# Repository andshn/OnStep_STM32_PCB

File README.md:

# OnStep STM32 PCB 

This is a PCB for [OnStep](https://github.com/hjd1964/OnStep),
designed for [1455N1201](https://www.hammfg.com/part/1455N1201) case.
In the board use XLR connectors for steper drivers.
The DB9 connector use for the hand controller.

The directory structure is as follows:
         
      onstep_pcb/       - KiCad project files for the board
      end_plates/       - Case end plates drawings as KiCad PCB files
      project_outputs/  - Gerbers, BOM, PDFs, etc

Note: this project contains partially modified elements
from the [KiCad Libraries](https://gitlab.com/kicad/libraries).

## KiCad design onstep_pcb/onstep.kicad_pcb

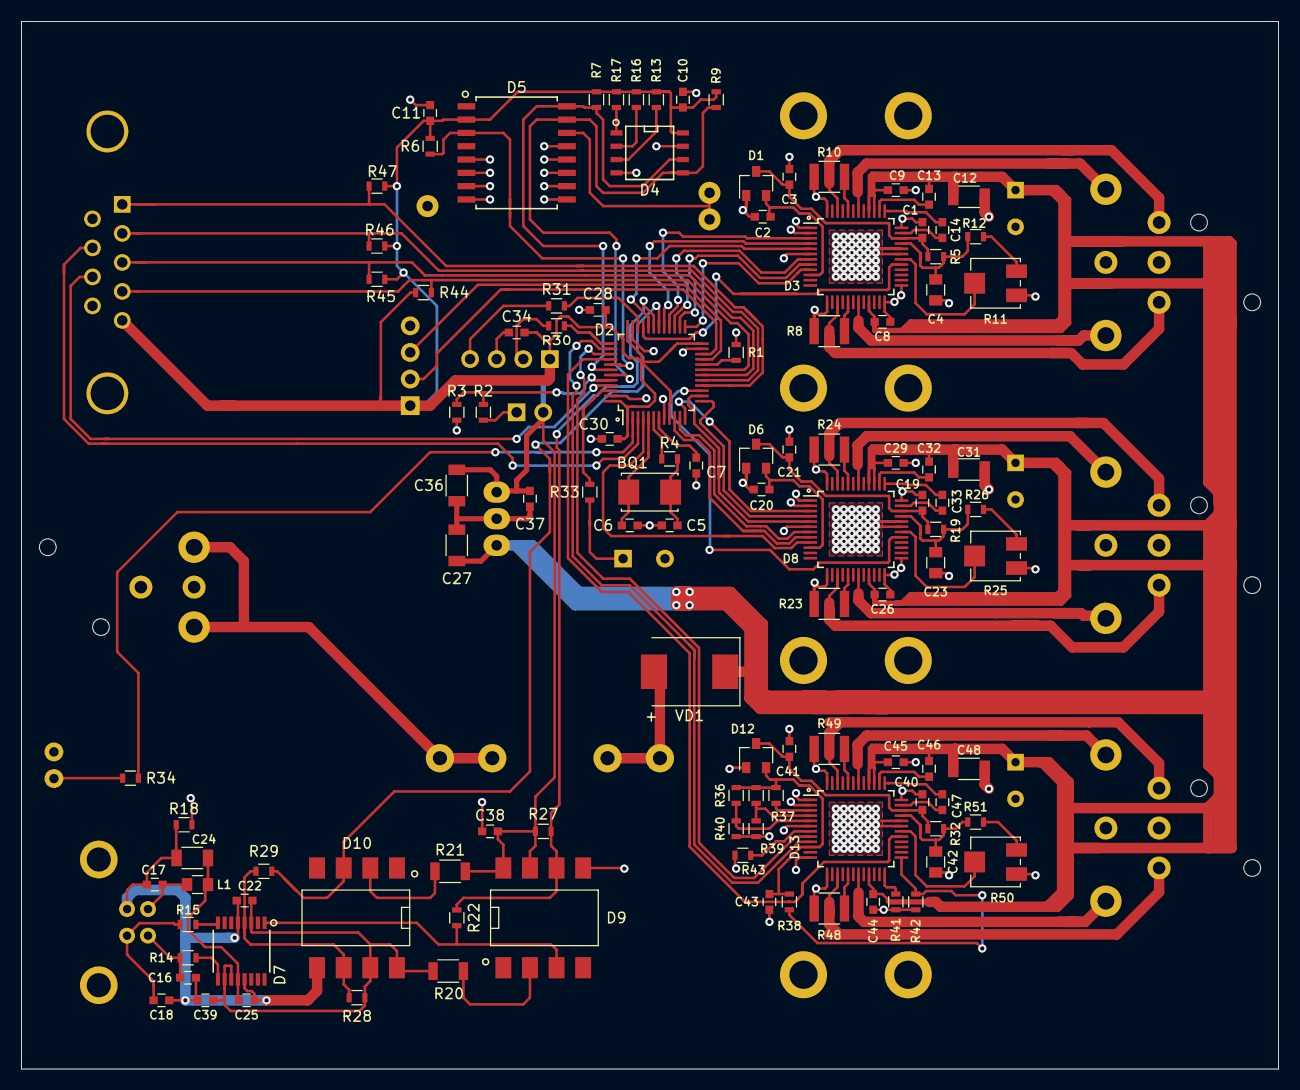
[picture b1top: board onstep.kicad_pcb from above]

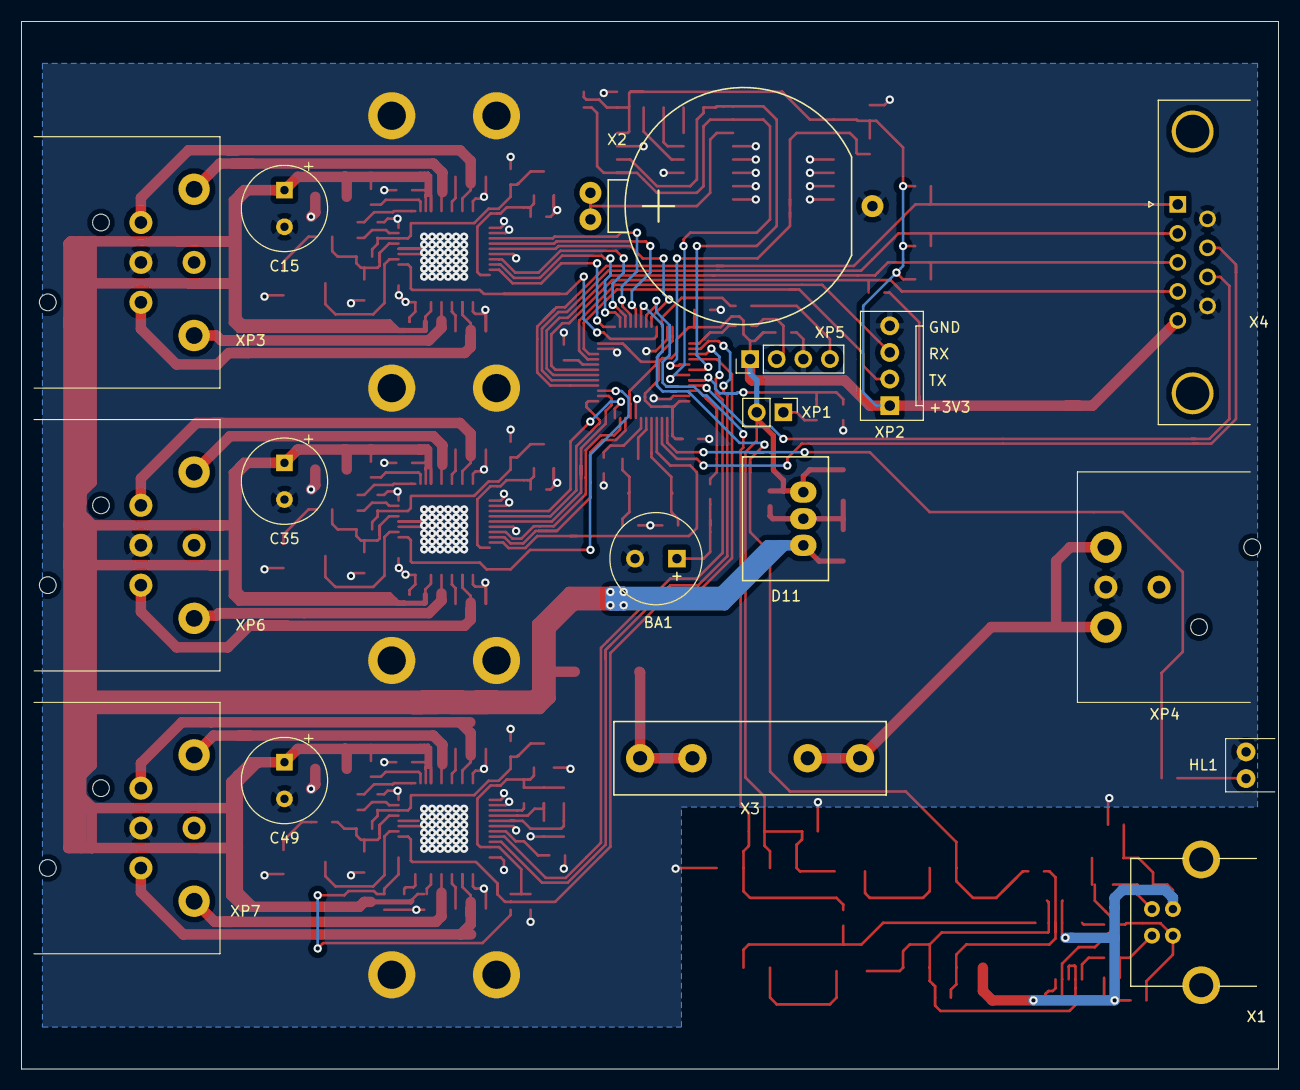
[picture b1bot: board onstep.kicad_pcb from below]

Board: 2 copper layers, 120.0 x 100.0 mm, 129 parts (17 on the bottom side), 114 nets.

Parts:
BA1: Speaker; Buzzer_CST-951AP
BQ1: 8 MHz; Crystal_SMD_5032-2pin_5.0x3.2mm
C1, C2, C3, C19, C20, C21, C40, C41, C43: 1 uF; C_0603
C4, C23, C42: 4.7 uF; C_0805
C5, C6: 24 pF; C_0603
C7, C8, C9, C10, C11, C13, C22, C25, C26, C28, C29, C30, C32, C34, C37, C38, C39, C44, C45, C46: 0.1 uF; C_0603
C12, C24, C31, C48: 4.7 uF; C_1206
C14, C33, C47: 0.022 uF; C_0603
C15, C35, C49: 100 uF; CP_Radial_D8.0mm_P3.50mm
C16, C18: 47 pF; C_0603
C17: 0.01 uF; C_0603
C27, C36: 10 uF; C_1206
D1, D6: MCP1700; SOT-23
D2: STM32F103C8T6; TQFP-48_7x7mm_Pitch0.5mm
D3, D8, D13: TMC2130; TQFP-48_7x7mm_Pitch0.5mm
D4: M24C32; SOIC-8-N
D5: DS3231; SOIC-16W_7.5x10.3mm_Pitch1.27mm
D7: FT230; SSOP-16_3.9x4.9mm_Pitch0.635mm
D9, D10: 6N137; SMD-8
D11: P78E03; CUI_P78E
D12: MCP1700T; SOT-23
HL1: LED; LED_WP934CB
L1: BLM21AG601SN1D; L_0805
R1, R2, R27, R28, R34: 1k; R_0603
R3, R6, R7, R9, R13, R16, R17: 10k; R_0603
R4: 390; R_0603
R5, R19, R32: 2.2; R_0603
R8, R10, R23, R24, R48, R49: 0.12; R_1210
R11, R25, R50: 20k; Potentiometer_Bourns_3314J_Vertical
R12, R26, R51: 20k; R_0603
R14, R15: 27; R_0603
R18, R22, R29, R35, R36, R39, R40, R42: DNI; R_0603
R20, R21: 220; R_1206
R30, R31: 100; R_0603
R33: 470; R_0603
R37, R38, R41, R43: 0; R_0603
R44, R45, R46, R47: 2.2k; R_0603
VD1: STPS5L60S; D_SMC
X1: "USB"; USB_B
X2: Battery Holder; CR2032_120591-1
X3: "FUSE"; Fuseholder5x20
X4: Conn_01x09; DSUB-9_Female_Horizontal_P2.77x2.84mm_EdgePinOffset9.90mm_H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
XP1: "Bootloader"; Pin_Header_Straight_1x02_Pitch2.54mm
XP2: "UART"; Pin_Header_640456-4
XP3: "DRV1"; NC5MBH
XP4: "12V"; NC3MAAH
XP5: "SWD"; Pin_Header_Straight_1x04_Pitch2.54mm
XP6: "DRV2"; NC5MBH
XP7: "DRV3"; NC5MBH

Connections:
+3,3V_USB: C22.2, C39.2, D7.3, D7.10, D7.11, D10.7, D10.8, R20.2, R28.2
+3V3: C10.2, C11.2, C28.2, C30.2, C34.2, C36.2, C37.2, C38.2, D2.1, D2.9, D2.24, D2.36, D2.48, D4.8, D5.2, D9.7, D9.8, D11.3, R6.2, R7.2, R9.2, R13.1, R16.1, R17.1, R21.2, R27.2, R44.1, R45.1, R46.1, R47.1, X4.5, XP1.2, XP2.1, XP5.1
+VM: C8.2, C9.2, C12.2, C13.2, C15.1, C26.2, C27.2, C29.2, C31.2, C32.2, C35.1, C44.2, C45.2, C46.2, C48.2, C49.1, D3.21, D3.39, D3.40, D8.21, D8.39, D8.40, D11.1, D13.21, D13.39, D13.40, VD1.1
/BOOT0: D2.44, R2.2, R3.2
/BOOT1: D2.20, R1.2
/DRV1_DIR: D2.25, D3.9
/DRV1_ENN: D2.33, D3.29
/DRV1_MISO: D2.27, D3.7
/DRV1_MOSI: D2.32, D3.5
/DRV1_NPCS: D2.28, D3.3
/DRV1_SPCK: D2.29, D3.4
/DRV1_STEP: D2.26, D3.8
/DRV2_DIR: D2.4, D8.9
/DRV2_ENN: D2.15, D8.29
/DRV2_MISO: D2.11, D8.7
/DRV2_MOSI: D2.14, D8.5
/DRV2_NPCS: D2.12, D8.3
/DRV2_SPCK: D2.13, D8.4
/DRV2_STEP: D2.10, D8.8
/DRV3_CFG0: D13.7, R43.2
/DRV3_CFG1: D13.5, R36.2, R40.2
/DRV3_CFG2: D13.4, R35.2, R39.2
/DRV3_CFG3: D13.3, R37.2
/DRV3_CFG4: D13.24, R41.2
/DRV3_CFG5: D13.25, R38.2, R42.2
/DRV3_DIR: D2.38, D13.9
/DRV3_ENN: D2.40, D13.29
/DRV3_STEP: D2.39, D13.8
/DRV3_VIO: C43.1, D12.2, D13.10, R35.1, R36.1, R37.1, R38.1
/HLED: D2.2, R34.2
/OSC_IN: BQ1.2, C6.2, D2.5
/OSC_OUT: D2.6, R4.2
/PECIDX: D2.3, X4.7
/RETICLE: D2.45, X4.8
/SCL: D2.42, D4.6, D5.16, R7.1
/SDA: D2.43, D4.5, D5.15, R9.1
/SQW: D2.41, D5.3, R6.1
/ST4_RA+: D2.19, R44.2, X4.4
/ST4_RA-: D2.16, R47.2, X4.1
/ST-4_DEC+: D2.18, R45.2, X4.3
/ST-4_DEC-: D2.17, R46.2, X4.2
/SWCLK: D2.37, R30.2
/SWDIO: D2.34, R31.2
/TONE: D2.46, R33.2
/UART0_RX: D2.30, D10.3, R29.1
/UART0_TX: D2.31, D9.6, R22.1, R27.1
/UART1_RX: D2.21, XP2.3
/UART1_TX: D2.22, XP2.2
GND: BA1.2, C1.1, C2.1, C3.1, C4.1, C5.1, C6.1, C7.1, C8.1, C9.1, C10.1, C11.1, C12.1, C15.2, C19.1, C20.1, C21.1, C23.1, C26.1, C27.1, C28.1, C29.1, C30.1, C31.1, C34.1, C35.2, C36.1, C37.1, C38.1, C40.1, C41.1, C42.1, C43.2, C44.1, C45.1, C48.1, C49.2, D1.1, D2.8, D2.23, D2.35, D2.47, D3.1, D3.2, D3.6, D3.13, D3.24, D3.25, D3.31, D3.32, D3.36, D3.48, D4.4, D4.7, D5.5, D5.6, D5.7, D5.8, D5.9, D5.10, D5.11, D5.12, D5.13, D6.1, D8.1, D8.2, D8.6, D8.13, D8.24, D8.25, D8.31, D8.32, D8.36, D8.48, D9.5, D11.2, D12.1, D13.1, D13.2, D13.6, D13.12, D13.13, D13.31, D13.32, D13.36, D13.48, HL1.1, R1.1, R3.1, R8.1, R10.1, R11.1, R18.1, R23.1, R24.1, R25.1, R39.1, R40.1, R41.1, R42.1, R43.1, R48.1, R49.1, R50.1, X2.2, X4.6, X4.9, XP2.4, XP3.6, XP4.3, XP5.3, XP6.6, XP7.6
GNDA: C16.1, C17.1, C18.1, C22.1, C24.1, C25.1, C39.1, D7.5, D7.13, D10.5, R18.2, X1.4
unnamed: BA1.1, R33.1
unnamed: BQ1.1, C5.2, R4.1
unnamed: C1.2, C3.2, D1.3, D3.34, R5.1
unnamed: C2.2, D1.2, D3.10
unnamed: C4.2, D3.33, R5.2, R12.1
unnamed: C7.2, D2.7
unnamed: C13.1, D3.38
unnamed: C14.1, D3.35
unnamed: C14.2, D3.37
unnamed: C16.2, R14.2, X1.2
unnamed: C17.2, L1.1, X1.1
unnamed: C18.2, R15.2, X1.3
unnamed: C19.2, C21.2, D6.3, D8.34, R19.1
unnamed: C20.2, D6.2, D8.10
unnamed: C23.2, D8.33, R19.2, R26.1
unnamed: C24.2, C25.2, D7.12, L1.2
unnamed: C32.1, D8.38
unnamed: C33.1, D8.35
unnamed: C33.2, D8.37
unnamed: C40.2, C41.2, D12.3, D13.34, R32.1
unnamed: C42.2, D13.33, R32.2, R51.1
unnamed: C46.1, D13.38
unnamed: C47.1, D13.35
unnamed: C47.2, D13.37
unnamed: D3.15, XP3.4
unnamed: D3.17, R8.2
unnamed: D3.19, XP3.5
unnamed: D3.30, R11.2
unnamed: D3.42, XP3.1
unnamed: D3.44, R10.2
unnamed: D3.46, XP3.2
unnamed: D4.1, R17.2
unnamed: D4.2, R16.2
unnamed: D4.3, R13.2
unnamed: D5.14, X2.1
unnamed: D7.1, D9.3, R22.2
unnamed: D7.8, R15.1
unnamed: D7.9, R14.1
unnamed: D8.15, XP6.4
unnamed: D8.17, R23.2
unnamed: D8.19, XP6.5
unnamed: D8.30, R25.2
unnamed: D8.42, XP6.1
unnamed: D8.44, R24.2
unnamed: D8.46, XP6.2
unnamed: D9.2, R20.1
unnamed: D10.2, R21.1
unnamed: D7.4, D10.6, R28.1, R29.2
unnamed: D13.15, XP7.4
unnamed: D13.17, R48.2
unnamed: D13.19, XP7.5
unnamed: D13.30, R50.2
unnamed: D13.42, XP7.1
unnamed: D13.44, R49.2
unnamed: D13.46, XP7.2
unnamed: HL1.2, R34.1
unnamed: R2.1, XP1.1
unnamed: R11.3, R12.2
unnamed: R25.3, R26.2
unnamed: R30.1, XP5.2
unnamed: R31.1, XP5.4
unnamed: R50.3, R51.2
unnamed: VD1.2, X3.1
unnamed: X3.2, XP4.1, XP4.2

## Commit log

2020-10-30 Added README.md and project_outputs
2020-10-30 Fixed README.md
